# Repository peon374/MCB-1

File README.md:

# MCB-1

This is a rebuild of the MCB-1 for anybody who has the sound card it connects to. I will improve the documentation around assembly once I have made one of the boards. Until the docs improve assume it is a work in progress. I will save gerbers in releases setup for JLCPCB. This board is entirely through hole design so should be easy to assemble.

# TODO

* [X] Layout rev0.1
* [ ] Make a board and get it tested
* [ ] Paint the Neutrik 6.5mm socket model
* [ ] Add an assembly and debugging guide

There have been a few modifications to improve availability of parts and reliability of operation.

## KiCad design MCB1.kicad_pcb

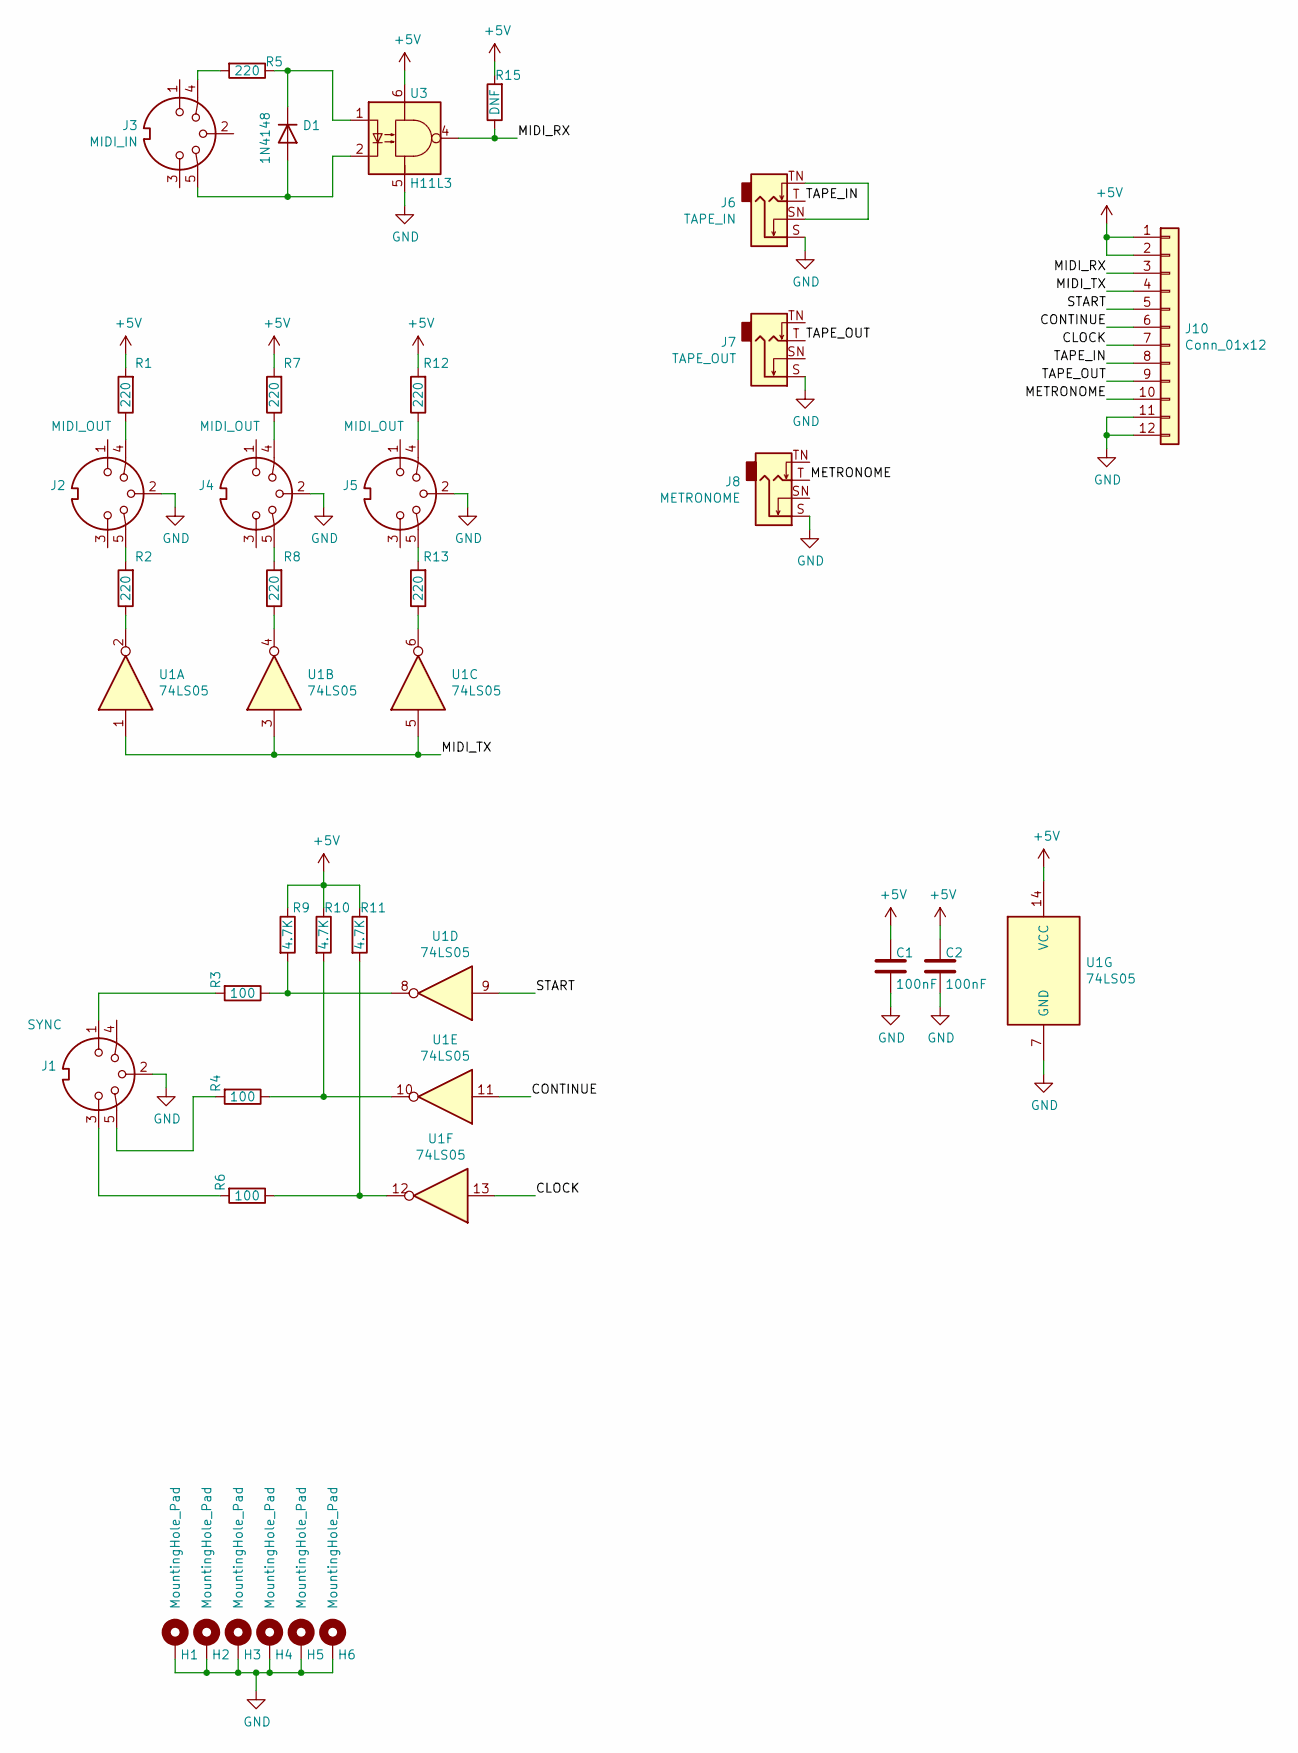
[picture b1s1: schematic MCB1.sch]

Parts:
C1, C2: 100nF; C_Disc_D4.7mm_W2.5mm_P5.00mm
D1: 1N4148; D_DO-35_SOD27_P3.81mm_Vertical_AnodeUp
H1, H2, H3, H4, H5, H6: MountingHole_Pad; MountingHole_3.2mm_M3_Pad_Via
J1: SYNC; SWITCHCRAFT_57PC5FS
J2, J4, J5: MIDI_OUT; SWITCHCRAFT_57PC5FS
J3: MIDI_IN; SWITCHCRAFT_57PC5FS
J6: TAPE_IN; Jack_6.35mm_Neutrik_NMJ4HFD3_Horizontal
J7: TAPE_OUT; Jack_6.35mm_Neutrik_NMJ4HFD3_Horizontal
J8: METRONOME; Jack_6.35mm_Neutrik_NMJ4HFD3_Horizontal
J10: Conn_01x12; PinHeader_2x06_P2.54mm_Vertical
R1, R2, R5, R7, R8, R12, R13: 220; R_Axial_DIN0204_L3.6mm_D1.6mm_P2.54mm_Vertical
R3, R4, R6: 100; R_Axial_DIN0204_L3.6mm_D1.6mm_P2.54mm_Vertical
R9, R10, R11: 4.7K; R_Axial_DIN0204_L3.6mm_D1.6mm_P2.54mm_Vertical
R15: DNF; R_Axial_DIN0204_L3.6mm_D1.6mm_P2.54mm_Vertical
U1: 74LS05; DIP-14_W7.62mm
U3: H11L3; DIP-6_W7.62mm

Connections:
+5V: C1.1, C2.1, J10.1, J10.2, R1.2, R7.2, R9.1, R10.1, R11.1, R12.2, R15.2, U1.14 (VCC), U3.6
/CLOCK: J10.7, U1.13
/CONTINUE: J10.6, U1.11
/METRONOME: J8.T, J10.10
/MIDI_RX: J10.3, R15.1, U3.4
/MIDI_TX: J10.4, U1.1, U1.3, U1.5
/START: J10.5, U1.9
/TAPE_IN: J6.T, J10.8
/TAPE_OUT: J7.T, J10.9
GND: C1.2, C2.2, H1.1, H2.1, H3.1, H4.1, H5.1, H6.1, J1.2, J2.2, J4.2, J5.2, J6.S, J7.S, J8.S, J10.11, J10.12, U1.7 (GND), U3.5
unnamed: D1.1 (K), R5.1, U3.1
unnamed: D1.2 (A), J3.5, U3.2
unnamed: J1.1, R3.2
unnamed: J1.3, R6.2
unnamed: J1.5, R4.2
unnamed: J2.4, R1.1
unnamed: J2.5, R2.2
unnamed: J3.4, R5.2
unnamed: J4.4, R7.1
unnamed: J4.5, R8.2
unnamed: J5.4, R12.1
unnamed: J5.5, R13.2
unnamed: J6.SN, J6.TN
unnamed: R2.1, U1.2
unnamed: R3.1, R9.2, U1.8
unnamed: R8.1, U1.4
unnamed: R4.1, R10.2, U1.10
unnamed: R6.1, R11.2, U1.12
unnamed: R13.1, U1.6

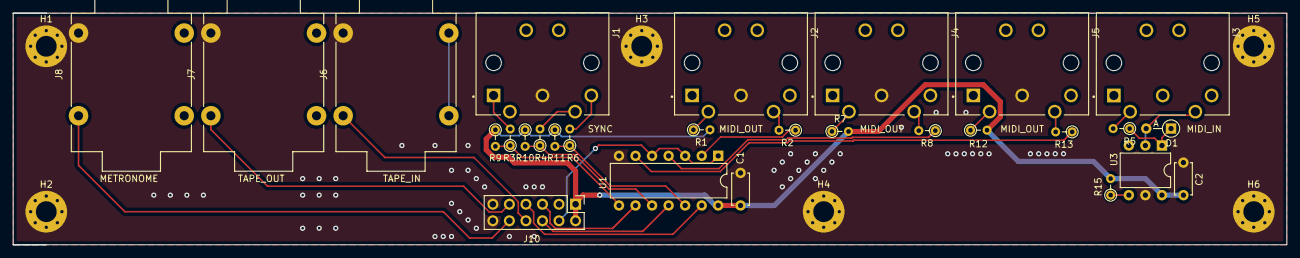
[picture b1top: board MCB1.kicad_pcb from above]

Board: 2 copper layers, 195.6 x 35.6 mm, 34 parts (0 on the bottom side), 29 nets.

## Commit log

2021-09-20 Initial add - work in progress
2021-09-20 Cleanup
2021-09-20 This board is worth building to test
